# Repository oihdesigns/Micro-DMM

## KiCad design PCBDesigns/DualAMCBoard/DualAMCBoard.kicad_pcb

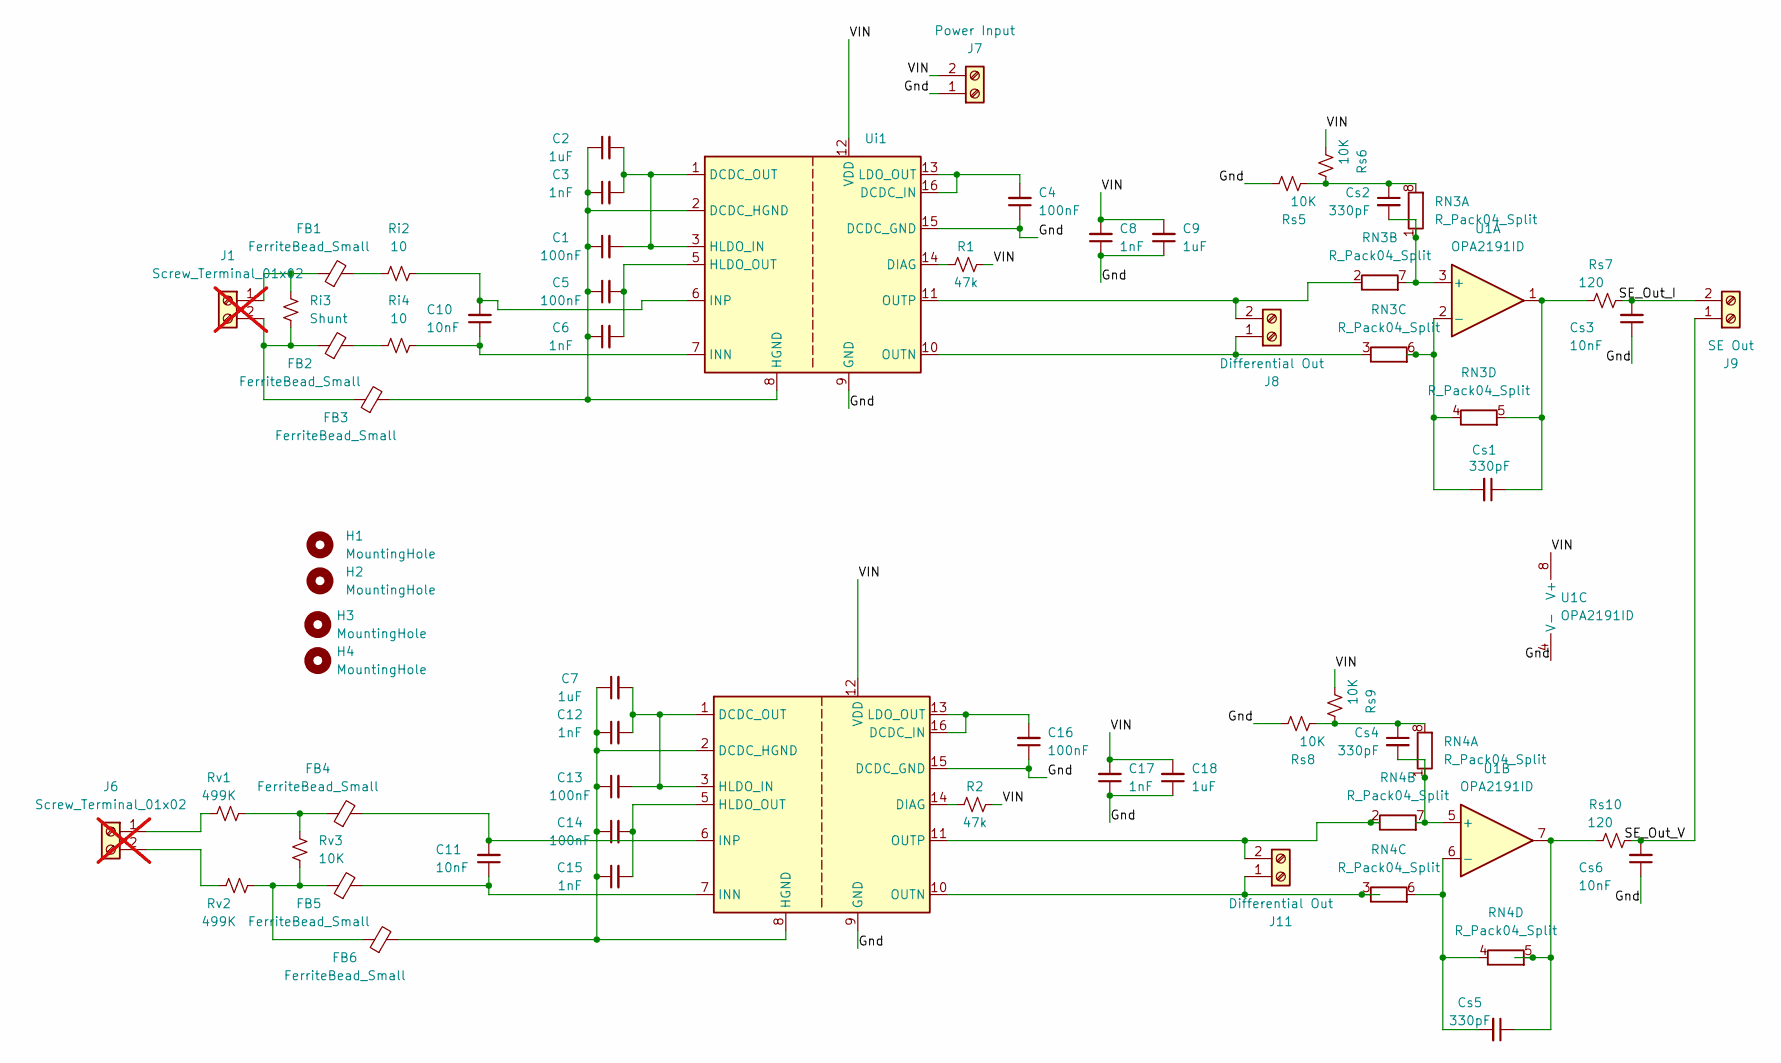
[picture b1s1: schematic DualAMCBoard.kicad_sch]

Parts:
C1, C4, C13, C16: 100nF; C_0603_1608Metric_Pad1.08x0.95mm_HandSolder
C2, C7: 1uF; C_0603_1608Metric_Pad1.08x0.95mm_HandSolder
C3, C12: 1nF; C_0603_1608Metric_Pad1.08x0.95mm_HandSolder
C5, C14: 100nF; C_1206_3216Metric_Pad1.33x1.80mm_HandSolder
C6, C8, C15, C17: 1nF; C_1206_3216Metric_Pad1.33x1.80mm_HandSolder
C9, C18: 1uF; C_1206_3216Metric_Pad1.33x1.80mm_HandSolder
C10, C11: 10nF; C_0805_2012Metric_Pad1.18x1.45mm_HandSolder
Cs1, Cs2, Cs4, Cs5: 330pF; C_0603_1608Metric_Pad1.08x0.95mm_HandSolder
Cs3, Cs6: 10nF; C_0805_2012Metric_Pad1.18x1.45mm_HandSolder
FB1, FB2, FB3, FB4, FB5, FB6: FerriteBead_Small; L_0402_1005Metric_Pad0.77x0.64mm_HandSolder
H1, H2, H3, H4: MountingHole; MountingHole_2.2mm_M2_DIN965_Pad_TopBottom
J1, J6: Screw_Terminal_01x02; TerminalBlock_RND_205-00232_1x02_P5.08mm_Horizontal; not fitted
J7: Power Input; TerminalBlock_Phoenix_MPT-0,5-2-2.54_1x02_P2.54mm_Horizontal
J8, J11: Differential Out; TerminalBlock_Phoenix_MPT-0,5-2-2.54_1x02_P2.54mm_Horizontal
J9: SE Out; TerminalBlock_Phoenix_MPT-0,5-2-2.54_1x02_P2.54mm_Horizontal
R1, R2: 47k; R_0805_2012Metric_Pad1.20x1.40mm_HandSolder
RN3, RN4: R_Pack04_Split; R_Array_Convex_4x0612
Ri2, Ri4: 10; R_0805_2012Metric_Pad1.20x1.40mm_HandSolder
Ri3: Shunt; R_2010_5025Metric_Pad1.40x2.65mm_HandSolder
Rs5, Rs6, Rs8, Rs9: 10K; R_0805_2012Metric_Pad1.20x1.40mm_HandSolder
Rs7, Rs10: 120; R_0805_2012Metric_Pad1.20x1.40mm_HandSolder
Rv1, Rv2: 499K; R_0805_2012Metric_Pad1.20x1.40mm_HandSolder
Rv3: 10K; R_0805_2012Metric_Pad1.20x1.40mm_HandSolder
U1: OPA2191ID; SOIC-8_3.9x4.9mm_P1.27mm
Ui1: AMC3301DWER; SOIC-16W_7.5x10.3mm_P1.27mm
Uv1: AMC3330QDWERQ1; SOIC-16W_7.5x10.3mm_P1.27mm

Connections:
/Gnd: C4.1, C8.1, C9.1, C16.1, C17.1, C18.1, Cs3.1, Cs6.1, J7.1, Rs5.1, Rs8.1, U1.4 (V-), Ui1.9 (GND), Ui1.15 (DCDC_GND), Uv1.9 (GND), Uv1.15 (DCDC_GND)
/SE_Out_I: Cs3.2, J9.2, Rs7.1
/SE_Out_V: Cs6.2, J9.1, Rs10.1
/VIN: C8.2, C9.2, C17.2, C18.2, J7.2, R1.1, R2.1, Rs6.2, Rs9.2, U1.8 (V+), Ui1.12 (VDD), Uv1.12 (VDD)
unnamed: FB1.2, Ri2.1
unnamed: FB2.2, Ri4.1
unnamed: FB4.1, Rv1.2, Rv3.1
unnamed: FB5.1, FB6.1, Rv2.1, Rv3.2
unnamed: FB1.1, J1.1, Ri3.2
unnamed: FB2.1, FB3.1, J1.2, Ri3.1
unnamed: J6.1, Rv1.1
unnamed: J6.2, Rv2.2
unnamed: J8.1, RN3.3 (R3.1), Ui1.10 (OUTN)
unnamed: J8.2, RN3.2 (R2.1), Ui1.11 (OUTP)
unnamed: J11.1, RN4.3 (R3.1), Uv1.10 (OUTN)
unnamed: J11.2, RN4.2 (R2.1), Uv1.11 (OUTP)
unnamed: Cs2.2, RN3.1 (R1.1), RN3.7 (R2.2), U1.3 (+)
unnamed: Cs2.1, RN3.8 (R1.2), Rs5.2, Rs6.1
unnamed: Cs1.2, RN3.4 (R4.1), RN3.6 (R3.2), U1.2 (-)
unnamed: Cs1.1, RN3.5 (R4.2), Rs7.2, U1.1
unnamed: Cs4.2, RN4.1 (R1.1), RN4.7 (R2.2), U1.5 (+)
unnamed: Cs4.1, RN4.8 (R1.2), Rs8.2, Rs9.1
unnamed: Cs5.2, RN4.4 (R4.1), RN4.6 (R3.2), U1.6 (-)
unnamed: Cs5.1, RN4.5 (R4.2), Rs10.2, U1.7
unnamed: C1.1, C2.1, C3.1, C5.1, C6.1, FB3.2, Ui1.2 (DCDC_HGND), Ui1.8 (HGND)
unnamed: C4.2, Ui1.13 (LDO_OUT), Ui1.16 (DCDC_IN)
unnamed: C1.2, C2.2, C3.2, Ui1.1 (DCDC_OUT), Ui1.3 (HLDO_IN)
unnamed: R1.2, Ui1.14 (DIAG)
unnamed: C5.2, C6.2, Ui1.5 (HLDO_OUT)
unnamed: C10.1, Ri4.2, Ui1.7 (INN)
unnamed: C10.2, Ri2.2, Ui1.6 (INP)
unnamed: C7.1, C12.1, C13.1, C14.1, C15.1, FB6.2, Uv1.2 (DCDC_HGND), Uv1.8 (HGND)
unnamed: C16.2, Uv1.13 (LDO_OUT), Uv1.16 (DCDC_IN)
unnamed: C7.2, C12.2, C13.2, Uv1.1 (DCDC_OUT), Uv1.3 (HLDO_IN)
unnamed: R2.2, Uv1.14 (DIAG)
unnamed: C14.2, C15.2, Uv1.5 (HLDO_OUT)
unnamed: C11.1, FB5.2, Uv1.7 (INN)
unnamed: C11.2, FB4.2, Uv1.6 (INP)

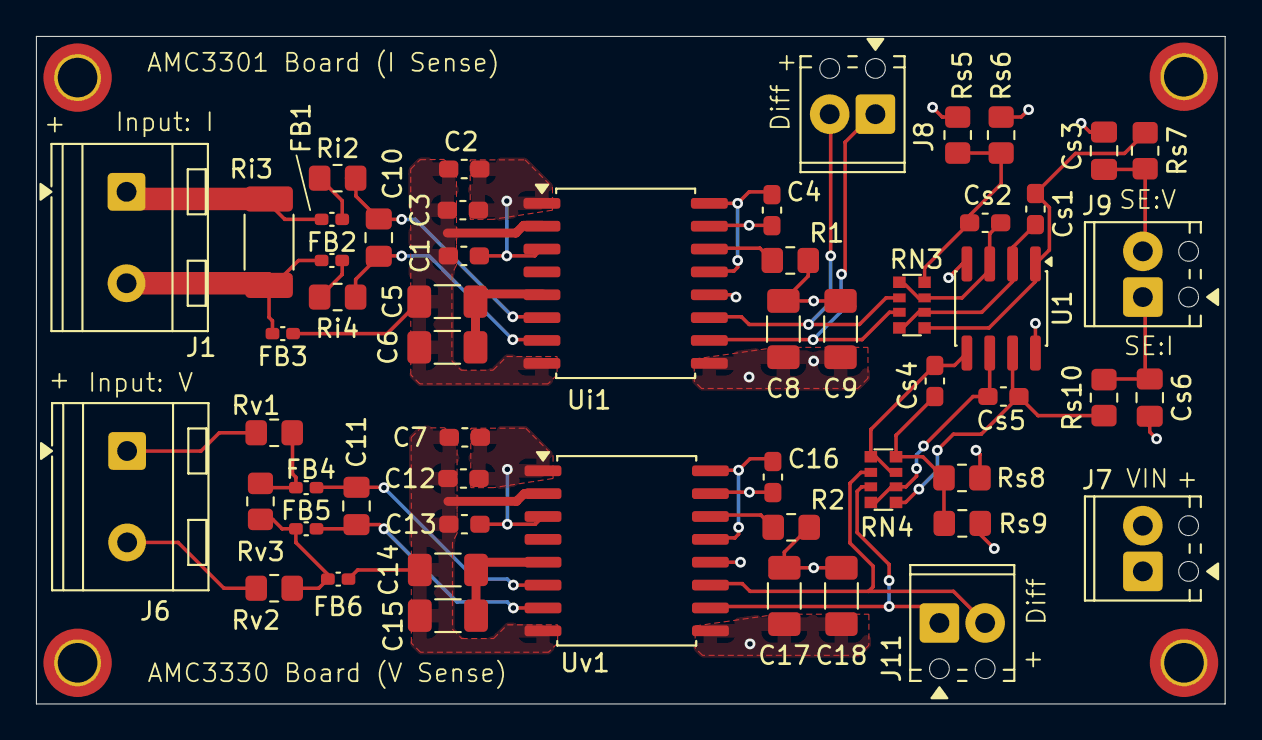
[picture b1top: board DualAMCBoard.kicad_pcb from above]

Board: 4 copper layers, 66.0 x 37.1 mm, 59 parts (0 on the bottom side), 38 nets.

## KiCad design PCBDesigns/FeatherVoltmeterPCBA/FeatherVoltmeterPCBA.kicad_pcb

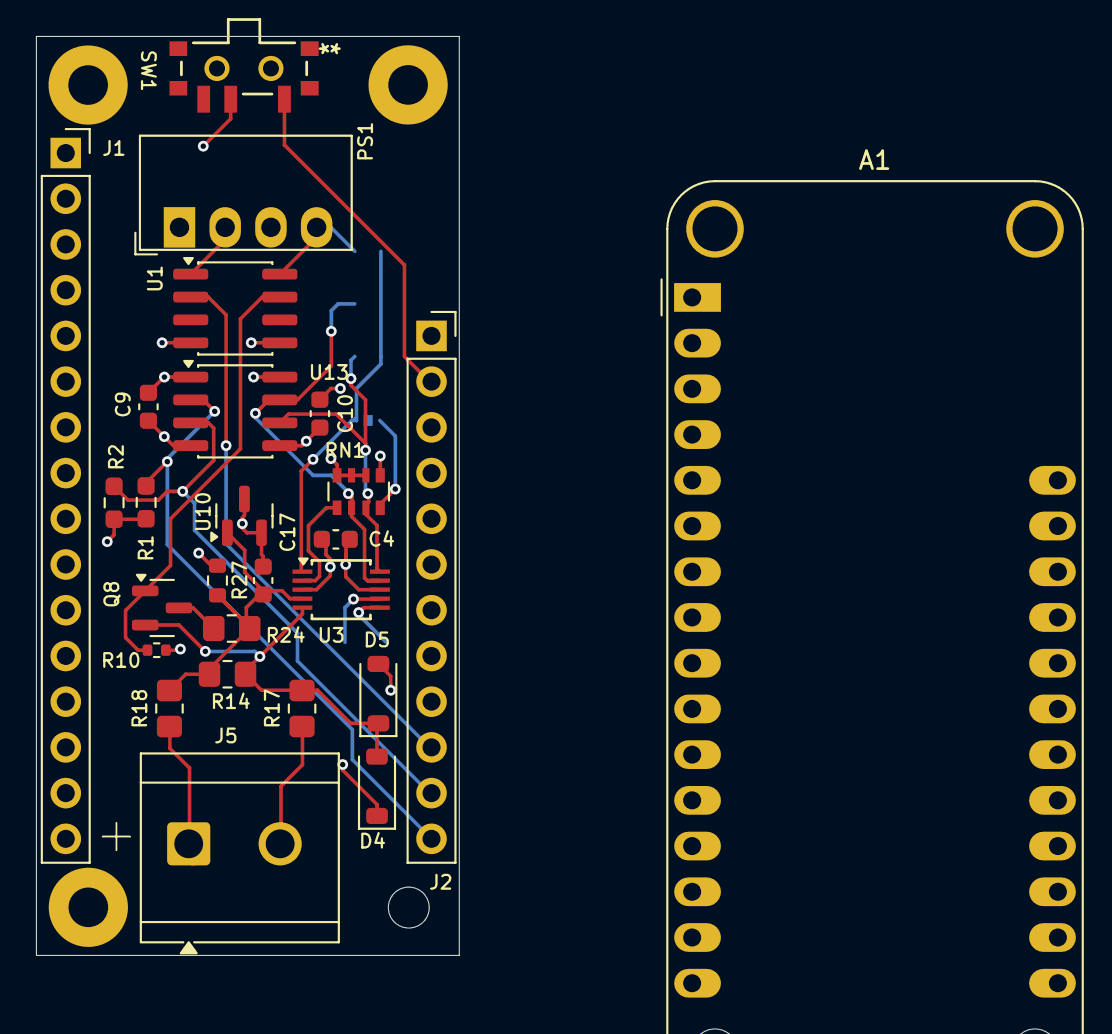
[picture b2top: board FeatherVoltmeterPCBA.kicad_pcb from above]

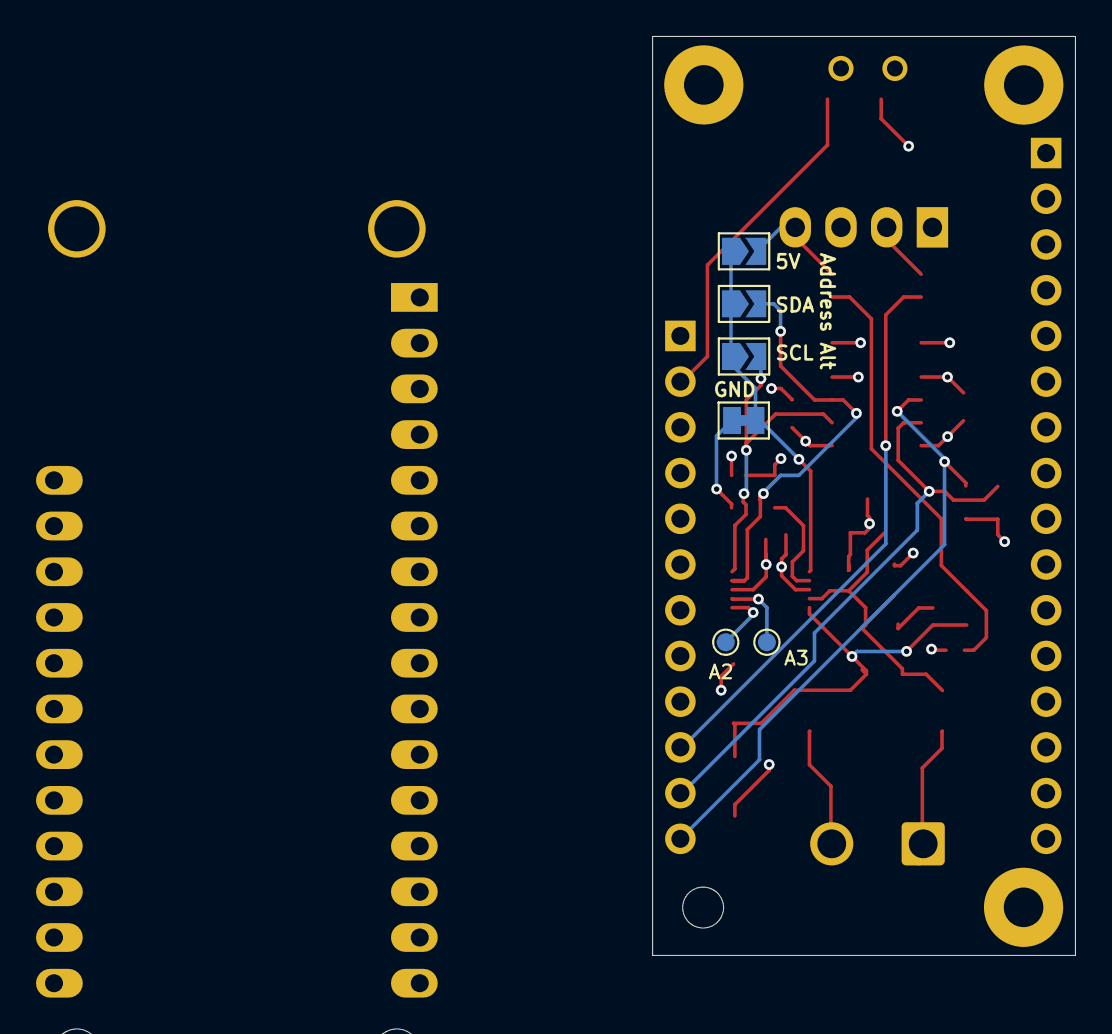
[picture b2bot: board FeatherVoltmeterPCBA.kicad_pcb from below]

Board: 4 copper layers, 23.5 x 51.1 mm, 35 parts (6 on the bottom side), 21 nets.

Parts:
A1: Adafruit_Feather_32u4_BluefruitLE; Adafruit_Feather_WithMountingHoles
A2, A3: TestPoint_Small; TestPoint_Pad_D1.0mm
C4, C9, C10, C17: 0.1uF; C_0603_1608Metric
D4, D5: D_Schottky; D_SOD-123
H1, H2, H3: MountingHole; MountingHole_2.2mm_M2_Pad
J1: Conn_01x16_Pin; PinSocket_1x16_P2.54mm_Vertical
J2: Conn_01x12_Pin; PinSocket_1x12_P2.54mm_Vertical
J5: Screw_Terminal_01x02; TerminalBlock_CUI_TB007-508-02_1x02_P5.08mm_Horizontal
JP1, JP2, JP3: Jumper_2_Small_Open; SolderJumper-2_P1.3mm_Open_TrianglePad1.0x1.5mm
JP4: Jumper_2_Small_Bridged; SolderJumper-2_P1.3mm_Bridged_Pad1.0x1.5mm
PS1: MEE1S0305SC; Converter_DCDC_Murata_MEE1SxxxxSC_THT
Q8: AO3400A MOSFET; SOT-23
R1, R2: 4.7K; R_0603_1608Metric_Pad0.98x0.95mm_HandSolder
R10: 75K; R_0402_1005Metric
R14: 1M; R_0805_2012Metric_Pad1.20x1.40mm_HandSolder
R17, R18: 499.0K; R_0805_2012Metric_Pad1.20x1.40mm_HandSolder
R24: 15K; R_0805_2012Metric_Pad1.20x1.40mm_HandSolder
R27: 4.7K; R_0603_1608Metric
RN1: R_Pack04_Split; R_Array_Convex_4x0603
SW1: SSSS811101; SW4_SSSS811101_ALPS
U1: ADuM1200AR; SOIC-8_3.9x4.9mm_P1.27mm
U3: ADS1015; TSSOP-10_3x3mm_P0.5mm
U10: LM4040DBZ-2.5; SOT-23
U13: ISO1540; SOIC-8_3.9x4.9mm_P1.27mm

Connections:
5V-iso: C4.2, C10.1, D4.1 (K), JP1.2 (B), PS1.4 (+Vout), R27.1, RN1.6 (R3.2), RN1.7 (R2.2), RN1.8 (R1.2), U1.8 (VDD2), U3.8 (VDD), U13.8 (VCC2)
/AIN0: C17.2, R14.1, R18.2, R24.2, R27.2, U3.4 (AIN0), U10.1 (K)
/AIN1: D4.2 (A), D5.1 (K), Q8.2 (S), R14.2, R17.2, U3.5 (AIN1)
/AIN2: A2.1 (1_1), U3.6 (AIN2)
/AIN3: A3.1 (1_1), U3.7 (AIN3)
/Gate_Control-iso: Q8.1 (G), R10.2, U1.7 (VOA)
/Signal1-MCU: A1.19 (D5), J2.10, U1.2 (VIA)
ADS_ADDR: JP1.1 (A), JP2.1 (A), JP3.1 (A), JP4.2 (B), U3.1 (ADDR)
ADS_ALERT: RN1.1 (R1.1), U3.2 (ALERT/RDY)
GND: A1.4 (GND), C9.2, J1.4, PS1.1 (-Vin), SW1.2, U1.4 (GND1), U13.4 (GND1)
Gnd-iso: C4.1, C10.2, C17.1, D5.2 (A), PS1.3 (-Vout), R10.1, RN1.5 (R4.2), U1.5 (GND2), U3.3 (GND), U10.2 (A), U10.3 (nc_(gnd)), U13.5 (GND2)
unnamed: A1.27 (EN), J2.2, SW1.1
unnamed: JP4.1 (A), RN1.4 (R4.1)
unnamed: Q8.3 (D), R24.1
SCL: A1.18 (SCL/D3), J2.11, R2.2, U13.3 (SCL1)
SCL-5V: JP3.2 (B), RN1.3 (R3.1), U3.10 (SCL), U13.6 (SCL2)
SDA: A1.17 (SDA/D2), J2.12, R1.2, U13.2 (SDA1)
SDA-5V: JP2.2 (B), RN1.2 (R2.1), U3.9 (SDA), U13.7 (SDA2)
VDD: A1.2 (3V3), C9.1, J1.2, PS1.2 (+Vin), R1.1, R2.1, U1.1 (VDD1), U13.1 (VCC1)
V_Input_Float: J5.2, R17.1
V_Input_REF: J5.1, R18.1

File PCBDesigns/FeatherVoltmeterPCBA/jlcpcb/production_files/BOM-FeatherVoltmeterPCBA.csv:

Comment,Designator,Footprint,LCSC,Quantity
0,R12,R_0805_2012Metric_Pad1.20x1.40mm_HandSolder,C17477,1
0.1uF,"C10,C17,C4,C9",C_0603_1608Metric,C14663,4
15K,R24,R_0805_2012Metric_Pad1.20x1.40mm_HandSolder,C473301,1
1M,R14,R_0805_2012Metric_Pad1.20x1.40mm_HandSolder,C445668,1
4.7K,"R1,R2,R27",R_0603_1608Metric_Pad0.98x0.95mm_HandSolder,C23162,3
499.0K,"R17,R18",R_0805_2012Metric_Pad1.20x1.40mm_HandSolder,C515730,2
75K,R10,R_0402_1005Metric,C25798,1
ADS1015,U3,TSSOP-10_3x3mm_P0.5mm,C193969,1
ADuM1200AR,U1,SOIC-8_3.9x4.9mm_P1.27mm,C15219,1
AO3400A MOSFET,Q8,SOT-23,C20917,1
D_Schottky,"D4,D5",D_SOD-123,C8598,2
ISO1540,U13,SOIC-8_3.9x4.9mm_P1.27mm,C179739,1
LM4040DBZ-2.5,U10,SOT-23,C44215,1
MEE1S0305SC,PS1,Converter_DCDC_Murata_MEE1SxxxxSC_THT,C7465186,1
R_Pack04_Split,RN1,R_Array_Convex_4x0603,C20197,1
SSSS811101,SW1,SW4_SSSS811101_ALPS,C109335,1
Screw_Terminal_01x02,J5,TerminalBlock_CUI_TB007-508-02_1x02_P5.08mm_Horizontal,C7509570,1
Conn_01x12_Pin,J2,PinSocket_1x12_P2.54mm_Vertical,,1
Conn_01x16_Pin,J1,PinSocket_1x16_P2.54mm_Vertical,,1
TestPoint_Small,A3,TestPoint_Pad_D1.0mm,,1
TestPoint_Small,A2,TestPoint_Pad_D1.0mm,,1

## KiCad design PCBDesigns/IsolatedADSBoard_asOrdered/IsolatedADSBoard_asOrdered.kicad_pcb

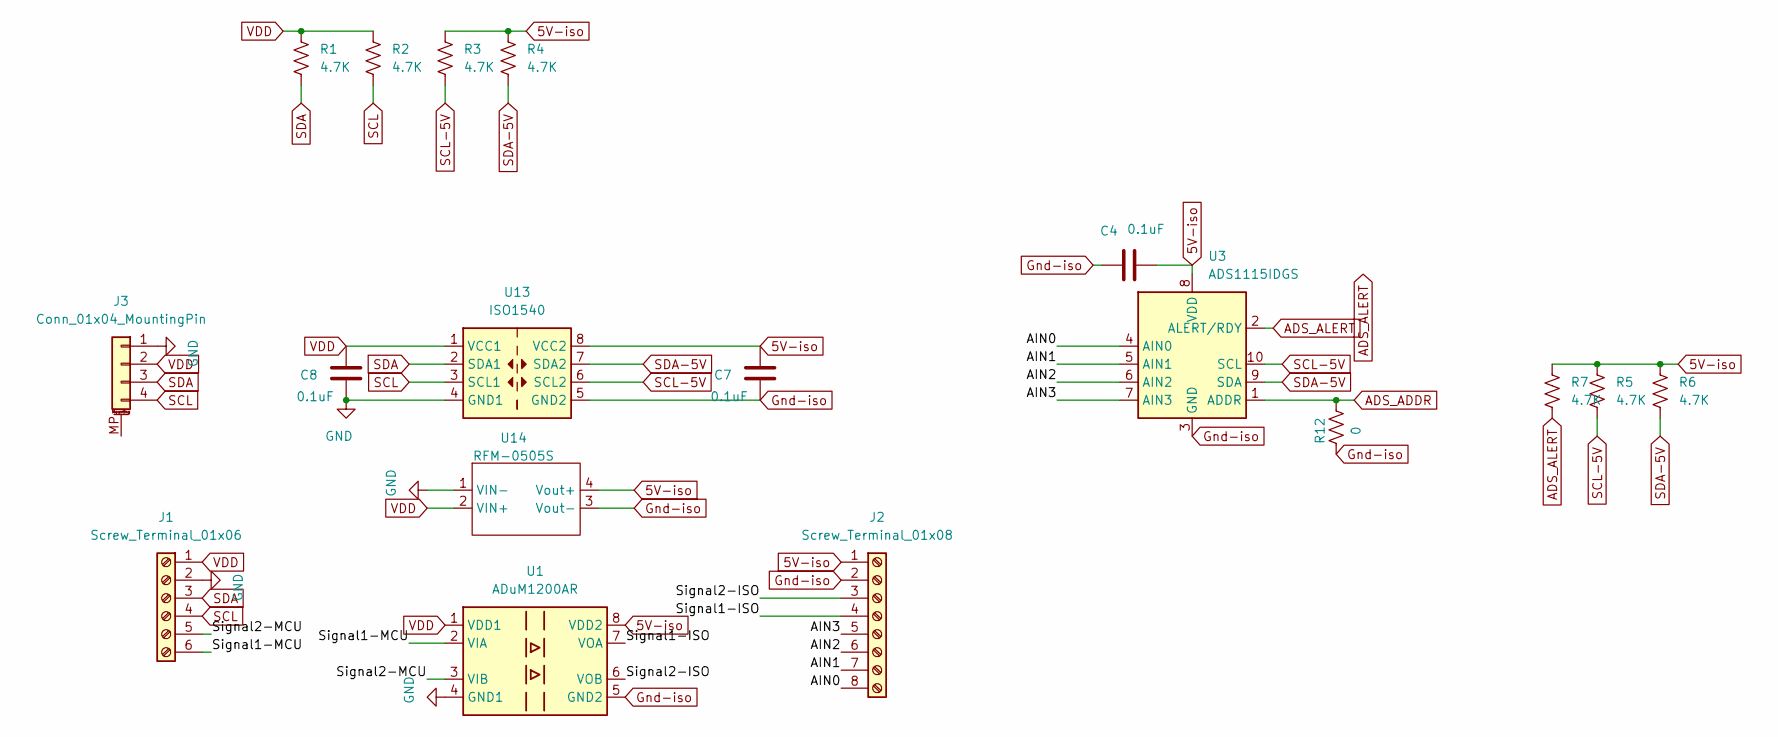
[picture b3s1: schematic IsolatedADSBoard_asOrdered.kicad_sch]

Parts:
C4, C7, C8: 0.1uF; C_0805_2012Metric_Pad1.18x1.45mm_HandSolder
J1: Screw_Terminal_01x06; PinHeader_1x06_P2.54mm_Vertical
J2: Screw_Terminal_01x08; PinHeader_1x08_P2.54mm_Vertical
J3: Conn_01x04_MountingPin; JST_SH_SM04B-SRSS-TB_1x04-1MP_P1.00mm_Horizontal
R1, R2, R3, R4, R5, R6, R7: 4.7K; R_0805_2012Metric_Pad1.20x1.40mm_HandSolder
R12: 0; R_0805_2012Metric_Pad1.20x1.40mm_HandSolder
U1: ADuM1200AR; SOIC-8_3.9x4.9mm_P1.27mm
U3: ADS1115IDGS; TSSOP-10_3x3mm_P0.5mm
U13: ISO1540; SOIC-8_3.9x4.9mm_P1.27mm
U14: RFM-0505S; XP SCT01F03S05

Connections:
5V-iso: C4.2, C7.1, J2.1, R3.1, R4.1, R5.1, R6.1, R7.1, U1.8 (VDD2), U3.8 (VDD), U13.8 (VCC2), U14.4 (Vout+)
/AIN0: J2.8, U3.4 (AIN0)
/AIN1: J2.7, U3.5 (AIN1)
/AIN2: J2.6, U3.6 (AIN2)
/AIN3: J2.5, U3.7 (AIN3)
/Signal1-ISO: J2.4, U1.7 (VOA)
/Signal1-MCU: J1.6, U1.2 (VIA)
/Signal2-ISO: J2.3, U1.6 (VOB)
/Signal2-MCU: J1.5, U1.3 (VIB)
ADS_ADDR: R12.1, U3.1 (ADDR)
ADS_ALERT: R7.2, U3.2 (ALERT/RDY)
GND: C8.2, J1.2, J3.1, U1.4 (GND1), U13.4 (GND1), U14.1 (VIN-)
Gnd-iso: C4.1, C7.2, J2.2, R12.2, U1.5 (GND2), U3.3 (GND), U13.5 (GND2), U14.3 (Vout-)
SCL: J1.4, J3.4, R2.2, U13.3 (SCL1)
SCL-5V: R3.2, R5.2, U3.10 (SCL), U13.6 (SCL2)
SDA: J1.3, J3.3, R1.2, U13.2 (SDA1)
SDA-5V: R4.2, R6.2, U3.9 (SDA), U13.7 (SDA2)
VDD: C8.1, J1.1, J3.2, R1.1, R2.1, U1.1 (VDD1), U13.1 (VCC1), U14.2 (VIN+)

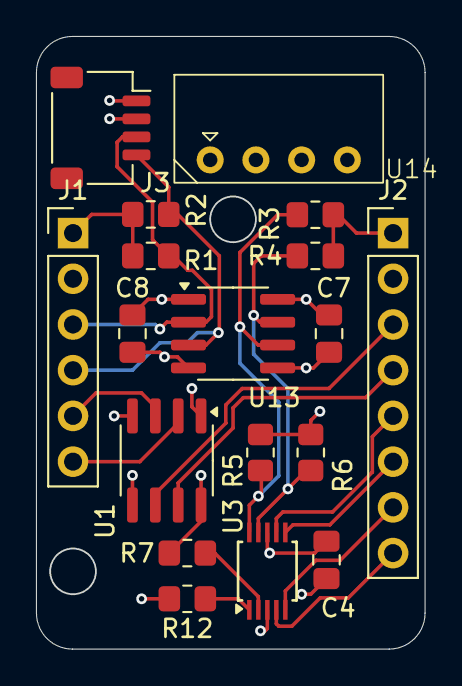
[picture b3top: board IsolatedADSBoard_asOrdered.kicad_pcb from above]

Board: 4 copper layers, 21.6 x 34.0 mm, 18 parts (0 on the bottom side), 18 nets.

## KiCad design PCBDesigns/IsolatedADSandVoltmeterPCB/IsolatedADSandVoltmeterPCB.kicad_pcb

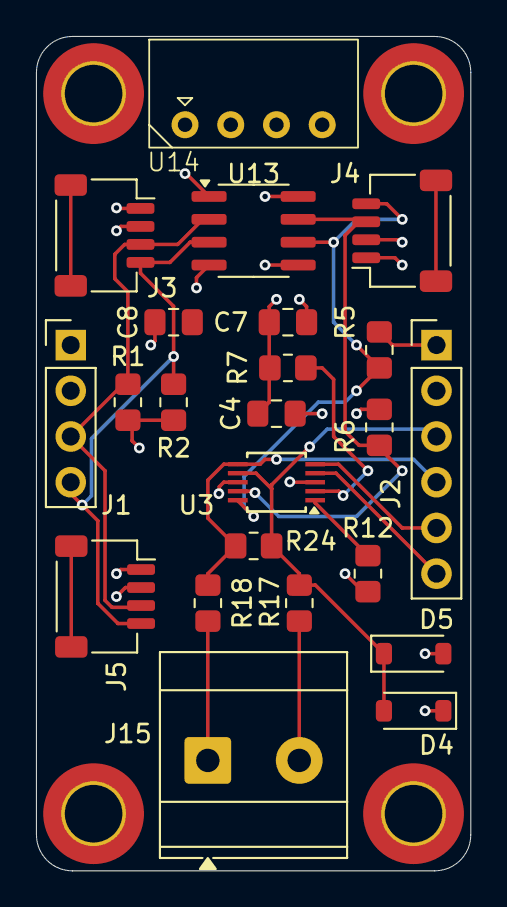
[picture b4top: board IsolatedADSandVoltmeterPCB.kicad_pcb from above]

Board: 4 copper layers, 24.1 x 46.4 mm, 27 parts (0 on the bottom side), 16 nets.

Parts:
C4, C7, C8: 0.1uF; C_0805_2012Metric_Pad1.18x1.45mm_HandSolder
D4, D5: D_Schottky; D_SOD-123
H1, H2, H3, H4: MountingHole; MountingHole_3.2mm_M3_DIN965_Pad_TopBottom
J1: Screw_Terminal_01x04; PinHeader_1x04_P2.54mm_Vertical
J2: Screw_Terminal_01x06; PinHeader_1x06_P2.54mm_Vertical
J3, J4, J5: Conn_01x04_MountingPin; JST_SH_SM04B-SRSS-TB_1x04-1MP_P1.00mm_Horizontal
J15: Barrel_Jack; TerminalBlock_Phoenix_MKDS-3-2-5.08_1x02_P5.08mm_Horizontal
R1, R2, R5, R6, R7: 4.7K; R_0805_2012Metric_Pad1.20x1.40mm_HandSolder
R12: 0; R_0805_2012Metric_Pad1.20x1.40mm_HandSolder
R17, R18: 499.0K; R_0805_2012Metric_Pad1.20x1.40mm_HandSolder
R24: 15K; R_0805_2012Metric_Pad1.20x1.40mm_HandSolder
U3: ADS1115IDGS; TSSOP-10_3x3mm_P0.5mm
U13: ISO1540; SOIC-8_3.9x4.9mm_P1.27mm
U14: RFM-0505S; XP SCT01F03S05

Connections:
5V-iso: C4.2, C7.1, D4.1 (K), J2.1, J4.2, R5.1, R6.1, R7.1, U3.8 (VDD), U13.8 (VCC2), U14.4 (Vout+)
/AIN0: J2.6, U3.4 (AIN0)
/AIN1: J2.5, U3.5 (AIN1)
/AIN2: J2.4, R18.2, R24.2, U3.6 (AIN2)
/AIN3: D4.2 (A), D5.1 (K), J2.3, R17.2, R24.1, U3.7 (AIN3)
ADS_ADDR: R12.1, U3.1 (ADDR)
ADS_ALERT: R7.2, U3.2 (ALERT/RDY)
GND: C8.2, J1.2, J3.1, J5.1, U13.4 (GND1), U14.1 (VIN-)
Gnd-iso: C4.1, C7.2, D5.2 (A), J2.2, J4.1, R12.2, U3.3 (GND), U13.5 (GND2), U14.3 (Vout-)
unnamed: J15.1, R18.1
unnamed: J15.2, R17.1
SCL: J1.4, J3.4, J5.4, R2.2, U13.3 (SCL1)
SCL-5V: J4.4, R5.2, U3.10 (SCL), U13.6 (SCL2)
SDA: J1.3, J3.3, J5.3, R1.2, U13.2 (SDA1)
SDA-5V: J4.3, R6.2, U3.9 (SDA), U13.7 (SDA2)
VDD: C8.1, J1.1, J3.2, J5.2, R1.1, R2.1, U13.1 (VCC1), U14.2 (VIN+)

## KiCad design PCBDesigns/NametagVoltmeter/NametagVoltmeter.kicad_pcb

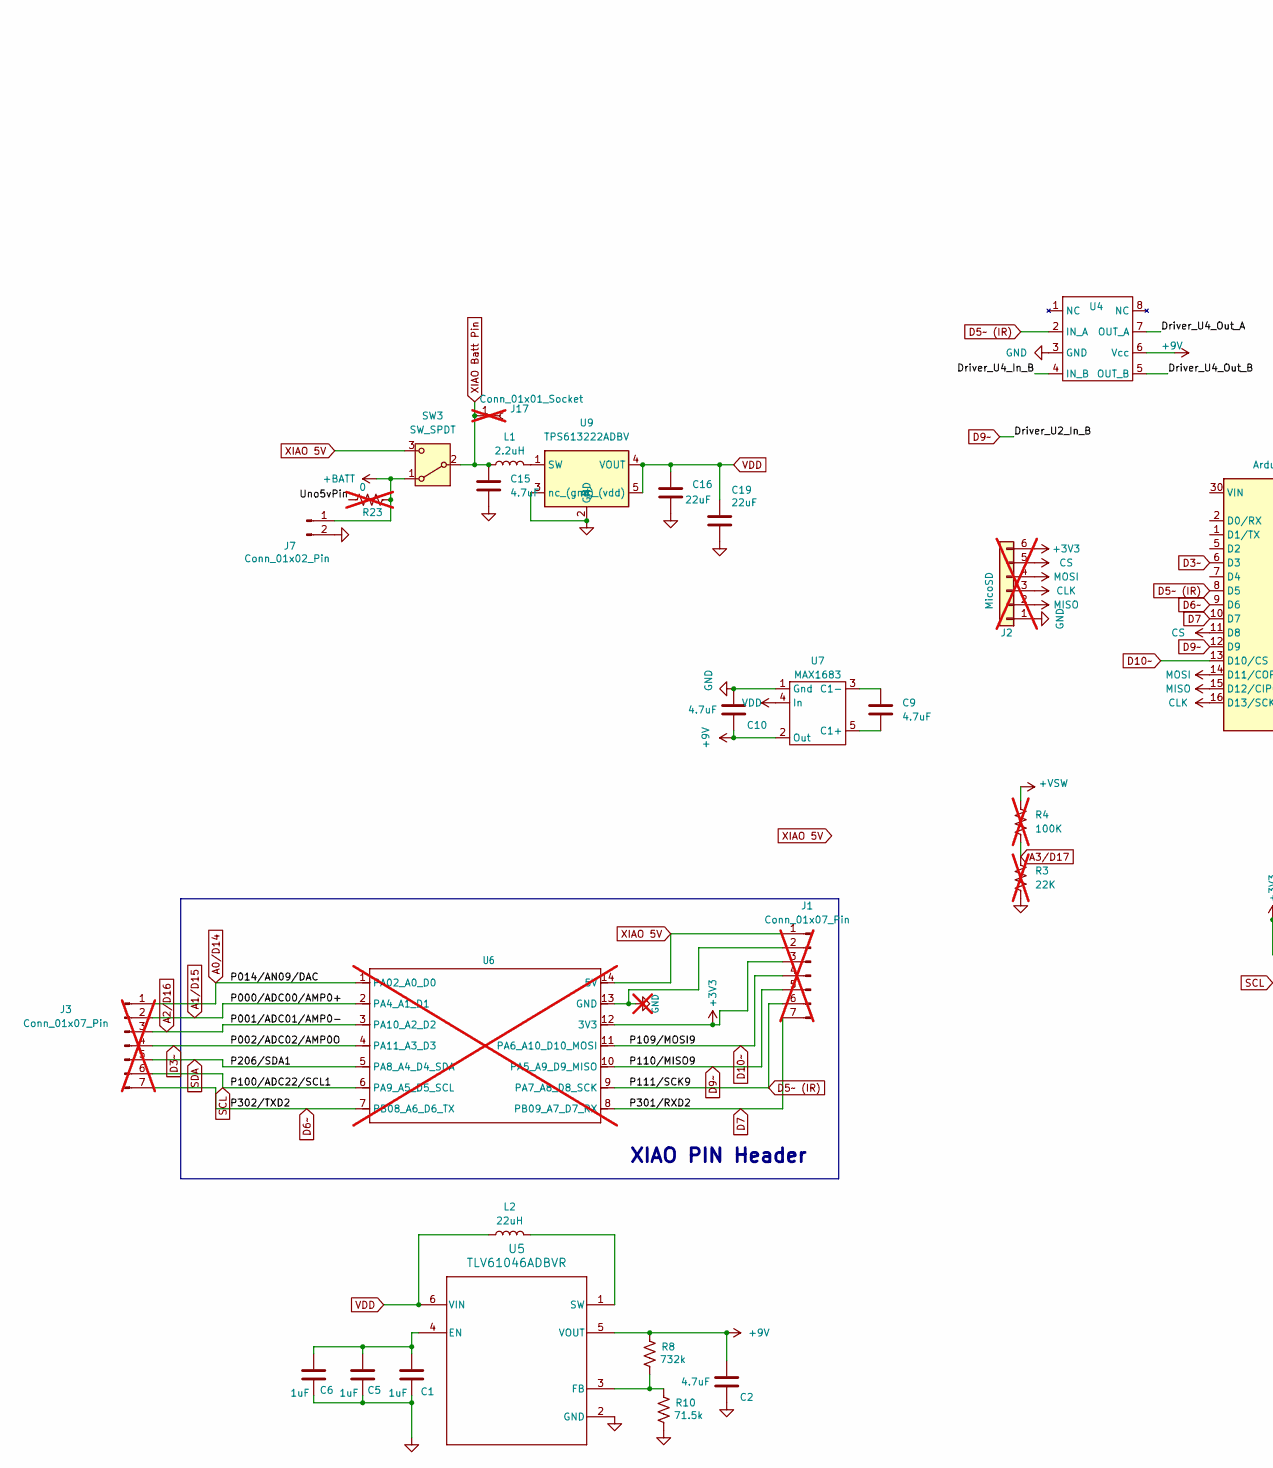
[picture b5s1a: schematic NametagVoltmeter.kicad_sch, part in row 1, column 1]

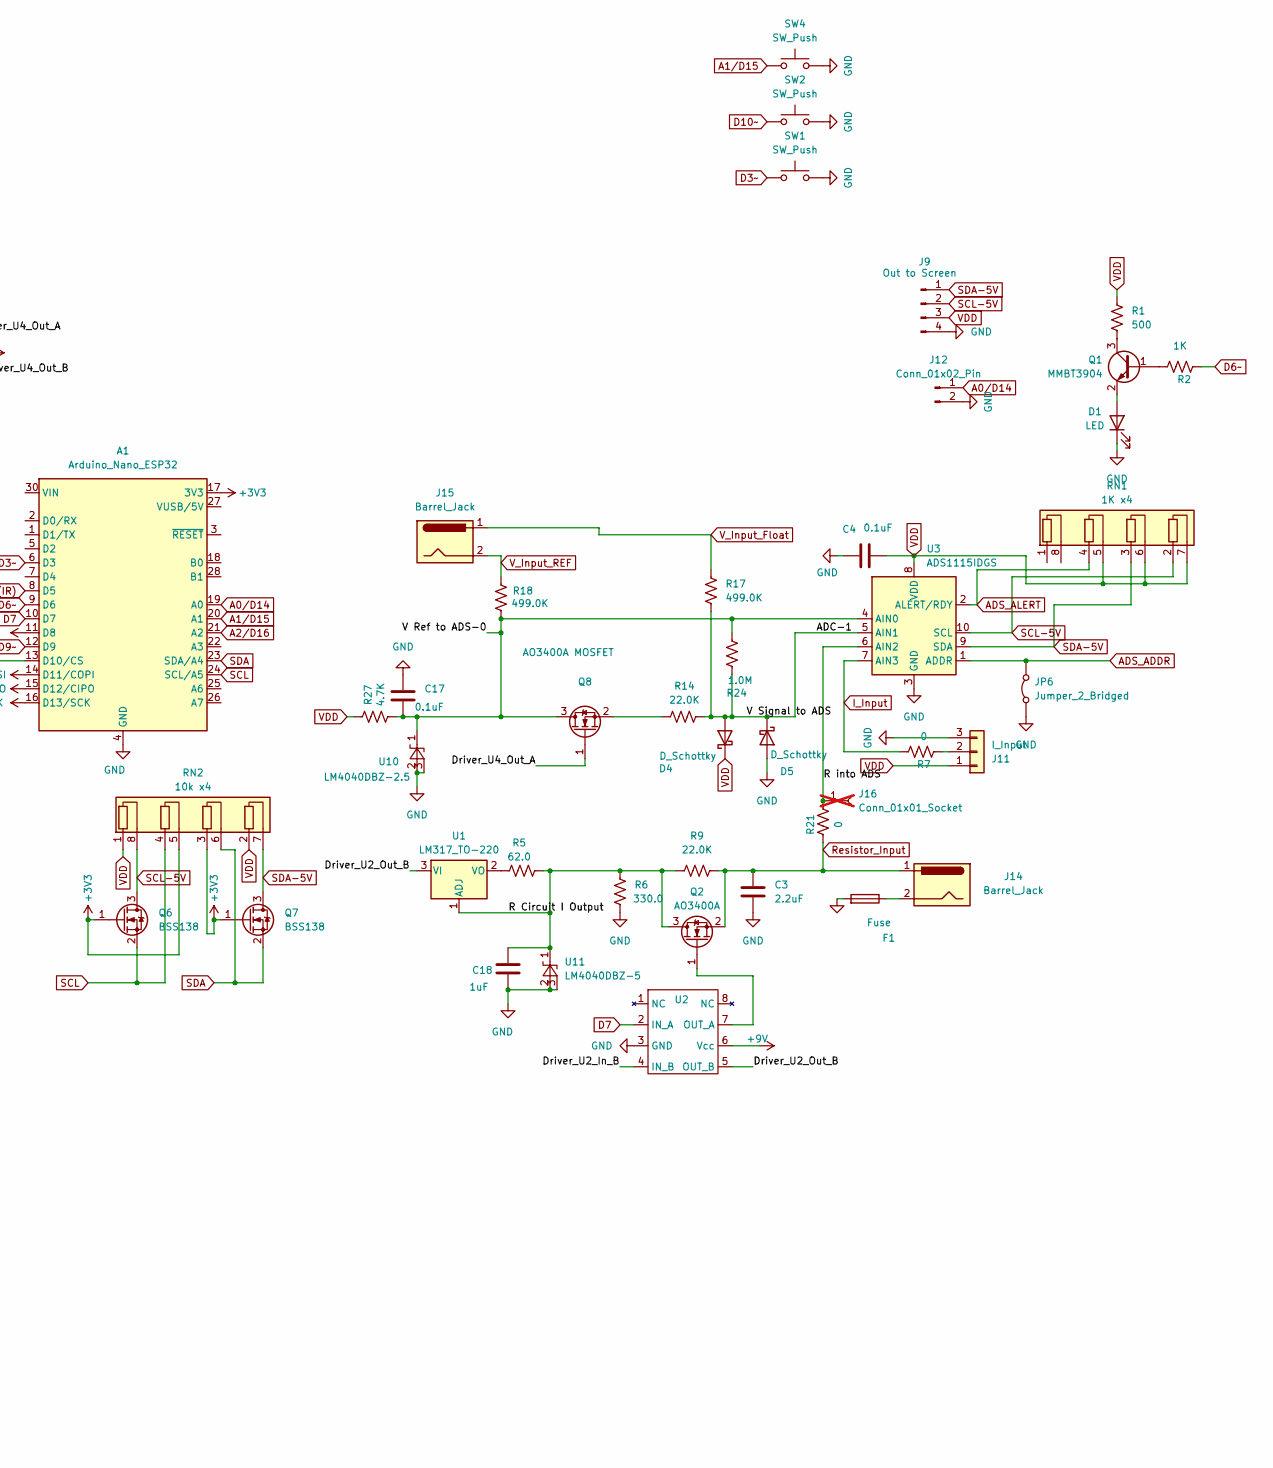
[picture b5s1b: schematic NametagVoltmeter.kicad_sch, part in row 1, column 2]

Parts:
A1: Arduino_Nano_ESP32; Arduino_Nano
C1, C5, C6, C18: 1uF; C_0805_2012Metric_Pad1.18x1.45mm_HandSolder
C2, C9, C10, C15: 4.7uF; C_0805_2012Metric_Pad1.18x1.45mm_HandSolder
C3: 2.2uF; C_0805_2012Metric_Pad1.18x1.45mm_HandSolder
C4, C17: 0.1uF; C_0805_2012Metric_Pad1.18x1.45mm_HandSolder
C16, C19: 22uF; C_0805_2012Metric_Pad1.18x1.45mm_HandSolder
D1: LED; LED_Luminus_MP-3030-1100_3.0x3.0mm
D4, D5: D_Schottky; D_SOD-123
F1: Fuse; Fuse_1206_3216Metric_Pad1.42x1.75mm_HandSolder
J1, J3: Conn_01x07_Pin; PinSocket_1x07_P2.54mm_Vertical; not fitted
J2: MicoSD; PinSocket_1x06_P2.54mm_Vertical; not fitted
J7, J12: Conn_01x02_Pin; PinSocket_1x02_P2.54mm_Vertical
J9: Out to Screen; PinSocket_1x04_P2.54mm_Vertical
J11: I_Input; PinSocket_1x03_P2.54mm_Vertical
J14, J15: Barrel_Jack; BarrelJack_Horizontal
J16, J17: Conn_01x01_Socket; PinSocket_1x01_P2.54mm_Vertical; not fitted
JP6: Jumper_2_Bridged; SolderJumper-2_P1.3mm_Bridged_Pad1.0x1.5mm
L1: 2.2uH; L_Murata_DFE201610P
L2: 22uH; L_Taiyo-Yuden_MD-5050
Q1: MMBT3904; SOT-23
Q2: AO3400A; SOT-23
Q6, Q7: BSS138; SOT-23
Q8: AO3400A MOSFET; SOT-23
R1: 500; R_0805_2012Metric_Pad1.20x1.40mm_HandSolder
R2: 1K; R_0805_2012Metric_Pad1.20x1.40mm_HandSolder
R3: 22K; R_0805_2012Metric_Pad1.20x1.40mm_HandSolder; not fitted
R4: 100K; R_0805_2012Metric_Pad1.20x1.40mm_HandSolder; not fitted
R5: 62.0; R_0805_2012Metric_Pad1.20x1.40mm_HandSolder
R6: 330.0; R_0805_2012Metric_Pad1.20x1.40mm_HandSolder
R7, R21: 0; R_0805_2012Metric_Pad1.20x1.40mm_HandSolder
R8: 732k; R_0805_2012Metric_Pad1.20x1.40mm_HandSolder
R9, R14: 22.0K; R_0805_2012Metric_Pad1.20x1.40mm_HandSolder
R10: 71.5k; R_0805_2012Metric_Pad1.20x1.40mm_HandSolder
R17, R18: 499.0K; R_0805_2012Metric_Pad1.20x1.40mm_HandSolder
R23: 0; R_0805_2012Metric_Pad1.20x1.40mm_HandSolder; not fitted
R24: 1.0M; R_0805_2012Metric_Pad1.20x1.40mm_HandSolder
R27: 4.7K; R_0805_2012Metric_Pad1.20x1.40mm_HandSolder
RN1: 1K x4; RESCAXS127P508X320X70-8N
RN2: 10k x4; RESCAXS127P508X320X70-8N
SW1, SW2, SW4: SW_Push; SW_SPST_CK_RS282G05A3
SW3: SW_SPDT; SW_Slide_SPDT_Angled_CK_OS102011MA1Q
U1: LM317_TO-220; SOT-223-3_TabPin2
U2, U4: IX4426N; SOIC-8_3.9x4.9mm_P1.27mm
U3: ADS1115IDGS; TSSOP-10_3x3mm_P0.5mm
U5: TLV61046ADBVR; SOT-23-6_Handsoldering
U6: not fitted
U7: MAX1683; SOT-23-5_HandSoldering
U9: TPS613222ADBV; SOT-23-5
U10: LM4040DBZ-2.5; SOT-23
U11: LM4040DBZ-5; SOT-23

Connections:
+3V3: A1.17 (3V3), J1.3, J2.6, Q6.1 (G), Q7.1 (G), RN2.3 (R3.1), RN2.5 (R2.2), U6.12 (3V3)
+9V: C2.1, C10.2, R8.1, U2.6 (Vcc), U4.6 (Vcc), U5.5 (VOUT), U7.2 (Out)
+BATT: J7.1, R23.2, SW3.1 (A)
+VSW: R4.2
/ADC-1: D4.2 (A), D5.1 (K), R14.2, R17.2, R24.1, U3.5 (AIN1)
/Driver_U2_Out_B: U1.3 (VI), U2.5 (OUT_B)
/Driver_U4_In_B: U4.4 (IN_B)
/Driver_U4_Out_A: Q8.1 (G), U4.7 (OUT_A)
/Driver_U4_Out_B: U4.5 (OUT_B)
/R Circuit I Output: C18.1, Q2.3 (D), R5.2, R6.2, R9.1, U1.1 (ADJ), U11.1 (K)
/R into ADS: J16.1, R21.1, U3.6 (AIN2)
/Uno5vPin: R23.1
/V Ref to ADS-0: C17.2, Q8.3 (D), R18.2, R24.2, R27.2, U3.4 (AIN0), U10.1 (K)
A0/D14: A1.19 (A0), J3.1, J12.1, U6.1 (PA02_A0_D0)
A1/D15: A1.20 (A1), J3.2, SW4.1, U6.2 (PA4_A1_D1)
A2/D16: A1.21 (A2), J3.3, U6.3 (PA10_A2_D2)
A3/D17: R3.2, R4.1
ADS_ADDR: JP6.2 (B), U3.1 (ADDR)
ADS_ALERT: RN1.4 (R2.1), U3.2 (ALERT/RDY)
CLK: A1.16 (D13/SCK), J2.3
CS: A1.11 (D8), J2.5
D3~: A1.6 (D3), J3.4, SW1.1, U6.4 (PA11_A3_D3)
D5~ (IR): A1.8 (D5), J1.6, U4.2 (IN_A), U6.9 (PA7_A8_D8_SCK)
D6~: A1.9 (D6), J3.7, R2.1, U6.7 (PB08_A6_D6_TX)
D7: A1.10 (D7), J1.7, U2.2 (IN_A), U6.8 (PB09_A7_D7_RX)
D9~: A1.12 (D9), J1.5, U2.4 (IN_B), U6.10 (PA5_A9_D9_MISO)
D10~: A1.13 (D10/CS), J1.4, SW2.1, U6.11 (PA6_A10_D10_MOSI)
GND: A1.4 (GND), A1.29 (GND), C1.2, C2.2, C3.2, C4.1, C5.2, C6.2, C10.1, C15.2, C16.2, C17.1, C18.2, C19.2, D1.1 (K), D5.2 (A), F1.2, J1.2, J2.1, J7.2, J9.4, J11.3, J12.2, JP6.1 (A), R3.1, R6.1, R10.2, SW1.2, SW2.2, SW4.2, U2.3 (GND), U3.3 (GND), U4.3 (GND), U5.2 (GND), U6.13 (GND), U7.1 (Gnd), U9.2 (GND), U9.3 (nc_(gnd)), U10.2 (A), U10.3 (nc_(gnd)), U11.2 (A), U11.3 (nc_(gnd))
I_Input: R7.1, U3.7 (AIN3)
MISO: A1.15 (D12/CIPO), J2.2
MOSI: A1.14 (D11/COPI), J2.4
unnamed: D1.2 (A), Q1.2 (E)
unnamed: F1.1, J14.2
unnamed: J11.2, R7.2
unnamed: Q1.1 (B), R2.2
unnamed: Q1.3 (C), R1.1
unnamed: Q2.1 (G), U2.7 (OUT_A)
unnamed: Q8.2 (S), R14.1
unnamed: R5.1, U1.2 (VO)
unnamed: C1.1, C5.1, C6.1, U5.4 (EN)
unnamed: R8.2, R10.1, U5.3 (FB)
unnamed: L2.2, U5.1 (SW)
unnamed: C9.2, U7.5 (C1+)
unnamed: C9.1, U7.3 (C1-)
unnamed: L1.2, U9.1 (SW)
Resistor_Input: C3.1, J14.1, Q2.2 (S), R9.2, R21.2
SCL: A1.24 (SCL/A5), J3.6, Q6.2 (S), RN2.4 (R2.1), U6.6 (PA9_A5_D5_SCL)
SCL-5V: J9.2, Q6.3 (D), RN1.2 (R4.1), RN2.8 (R1.2), U3.10 (SCL)
SDA: A1.23 (SDA/A4), J3.5, Q7.2 (S), RN2.6 (R3.2), U6.5 (PA8_A4_D4_SDA)
SDA-5V: J9.1, Q7.3 (D), RN1.3 (R3.1), RN2.7 (R4.2), U3.9 (SDA)
VDD: C4.2, C16.1, C19.1, D4.1 (K), J9.3, J11.1, L2.1, R1.2, R27.1, RN1.5 (R2.2), RN1.6 (R3.2), RN1.7 (R4.2), RN2.1 (R1.1), RN2.2 (R4.1), U3.8 (VDD), U5.6 (VIN), U7.4 (In), U9.4 (VOUT), U9.5 (nc_(vdd))
V_Input_Float: J15.1, R17.1
V_Input_REF: J15.2, R18.1
XIAO 5V: J1.1, SW3.3 (C), U6.14 (5V)
XIAO Batt Pin: C15.1, J17.1, L1.1, SW3.2 (B)

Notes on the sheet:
XIAO PIN Header

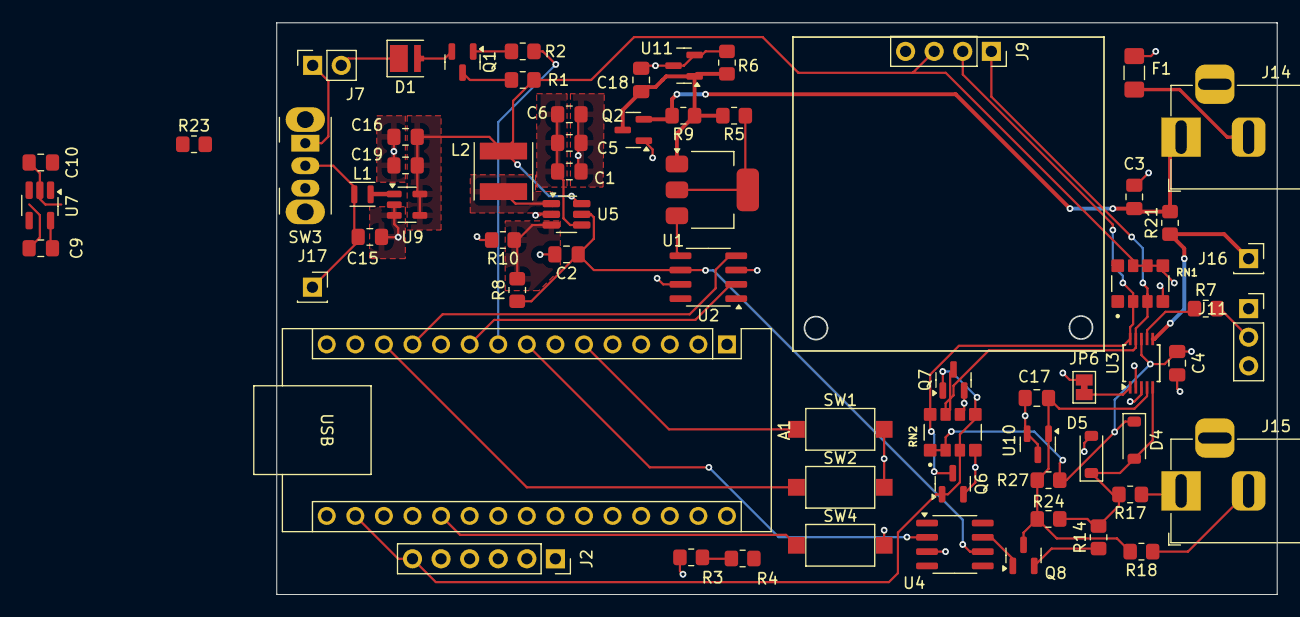
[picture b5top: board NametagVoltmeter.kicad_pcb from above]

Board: 4 copper layers, 88.9 x 50.8 mm, 66 parts (0 on the bottom side), 48 nets.
